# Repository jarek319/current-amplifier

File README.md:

# current-amplifier
Useful for measuring circuit consumption under low-power conditions

While experimenting with low-power sleep modes for other projects, I was running into issues measuring current using normal multimeters and oscilloscopes.

This amplifier doesn't create a significant effect on the circuit being tested, and allows for a very high resolution image of how different sleep strategies perform in circuit.

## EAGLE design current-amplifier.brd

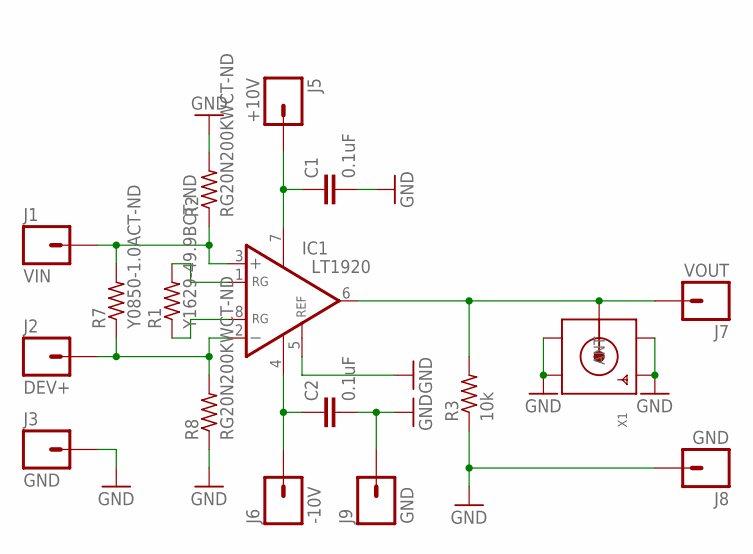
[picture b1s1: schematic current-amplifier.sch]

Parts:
C1, C2: 0.1uF; C0805
IC1: LT1920; SOIC8
J1: VIN; 1X01
J2: DEV+; 1X01
J3, J8, J9: GND; 1X01
J5: +10V; 1X01
J6: -10V; 1X01
J7: VOUT; 1X01
R1: Y1629-49.9BCT-ND; R0805
R2, R8: RG20N200KWCT-ND; R0805
R3: 10k; R0805
R7: Y0850-1.0ACT-ND; R2516WIDE
X1: SMACONNECTOR_EDGE; SMA_EDGELAUNCH

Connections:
GND: C1.2, C2.2, IC1.5 (REF), J3.1, J8.1, J9.1, R2.2, R3.1, R8.1, X1.GND@1 (GND4), X1.GND@2 (GND3), X1.GND@3 (GND2), X1.GND@4 (GND1)
unnamed: C1.1, IC1.7 (V+), J5.1
unnamed: C2.1, IC1.4 (V-), J6.1
unnamed: IC1.1 (RG), R1.2
unnamed: IC1.8 (RG), R1.1
unnamed: IC1.6 (OUT), J7.1, R3.2, X1.P (ANT)
unnamed: IC1.3 (+IN), J1.1, R2.1, R7.B1 (2), R7.B2 (2)
unnamed: IC1.2 (-IN), J2.1, R7.A1 (1), R7.A2 (1), R8.2

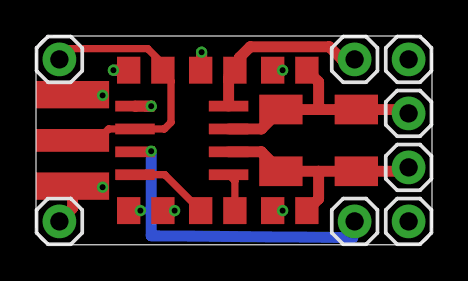
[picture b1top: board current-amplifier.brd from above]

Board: 2 copper layers, 22.0 x 11.6 mm, 17 parts (0 on the bottom side), 8 nets.

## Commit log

2018-07-05 design tested: working

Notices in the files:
parts and their libraries:
SparkFun-Connectors: Licensing: Creative Commons ShareAlike 4.0 International - https://creativecommons.org/licenses/by-sa/4.0
